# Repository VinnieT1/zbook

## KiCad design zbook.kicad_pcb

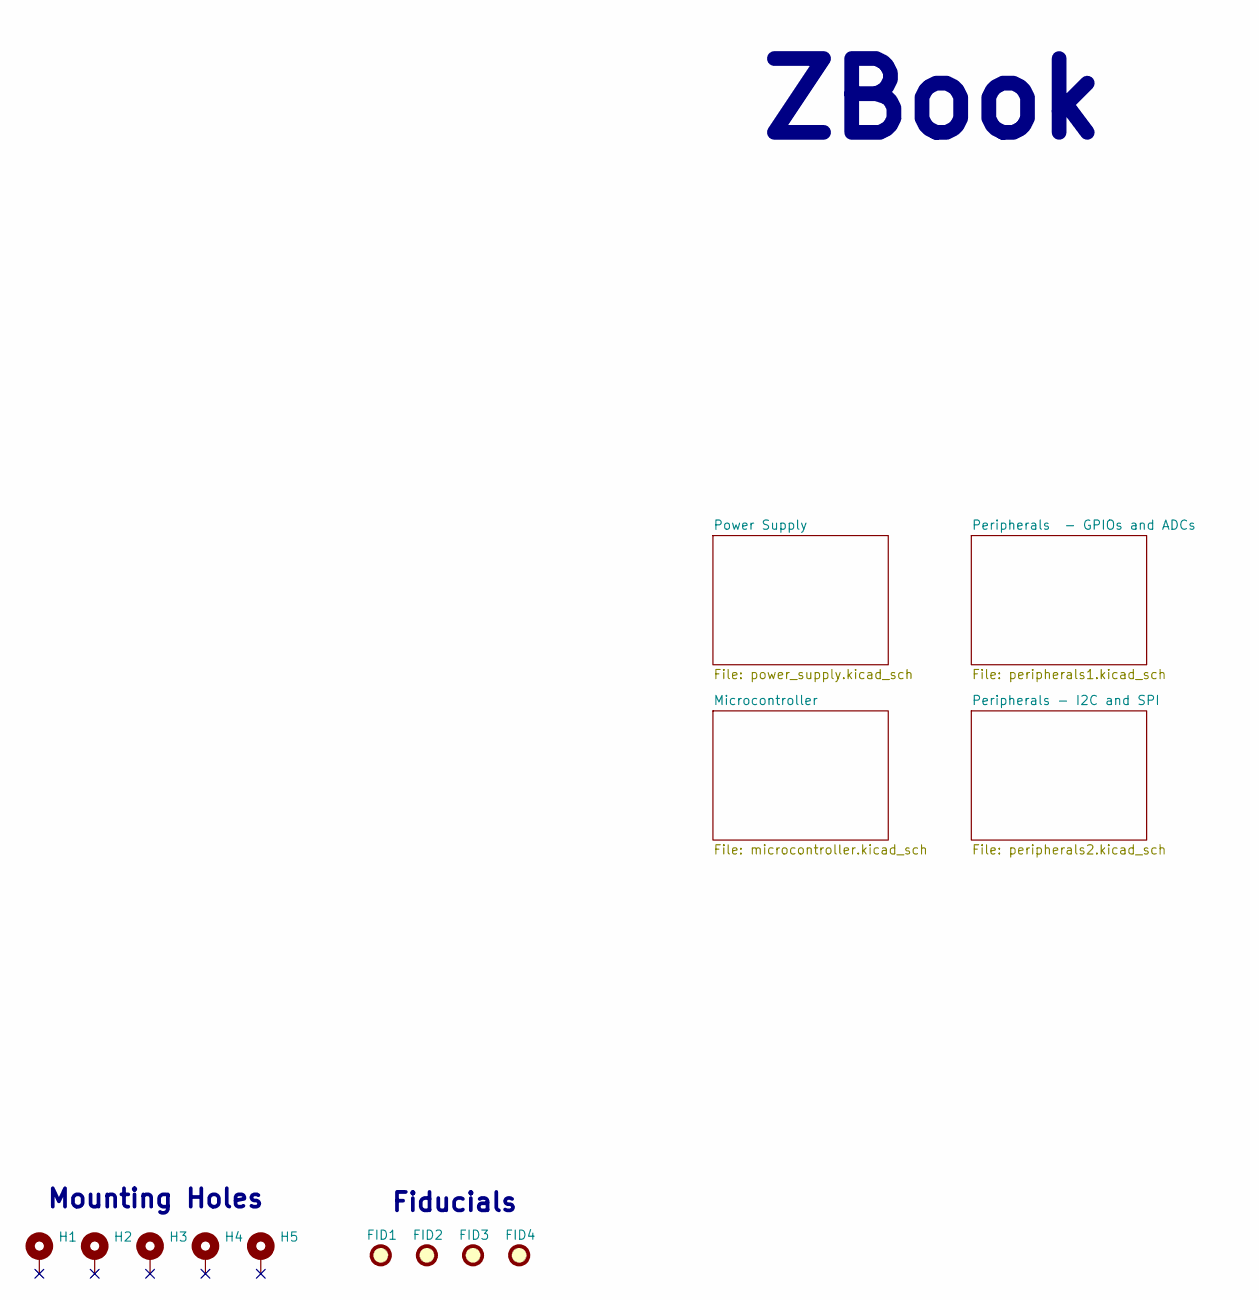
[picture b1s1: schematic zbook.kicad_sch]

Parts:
FID1, FID2, FID3, FID4: Fiducial; Fiducial_1mm_Mask3mm
H1, H2, H3, H4, H5: MountingHole_Pad; MountingHole_3.2mm_M3

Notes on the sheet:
ZBook
Fiducials
Mounting Holes

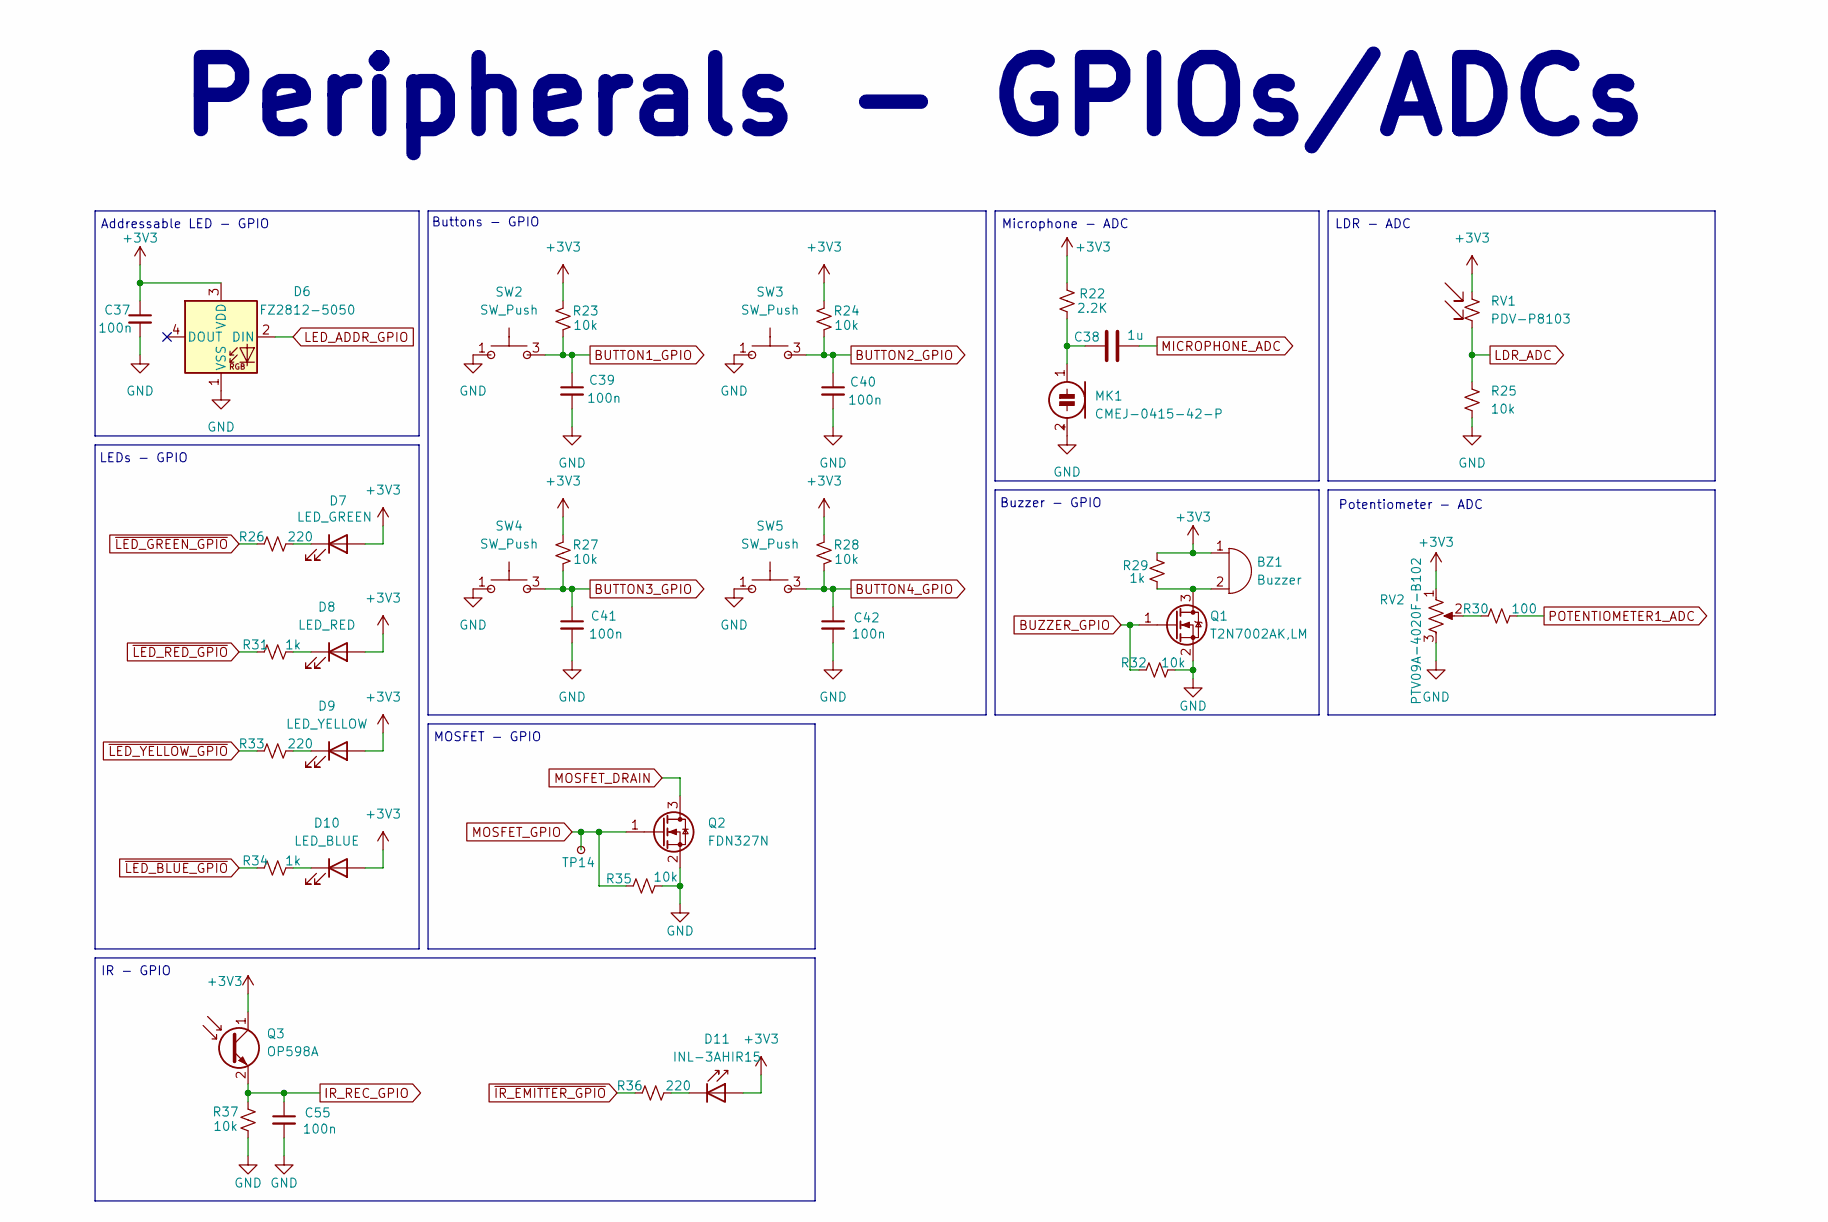
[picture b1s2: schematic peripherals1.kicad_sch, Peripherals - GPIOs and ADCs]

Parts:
BZ1: Buzzer; PS1440P02BT; MPN PS1440P02BT
C37, C39, C40, C41, C42, C55: 100n; C_0402_1005Metric; MPN CL05B104KA5NNNC
C38: 1u; C_0402_1005Metric; MPN CL05A105KO5NNNC
D6: FZ2812-5050; LED_FZ2812-5050; MPN FZ2812-5050
D7: LED_GREEN; LED_0603_1608Metric; MPN LG Q976.01-MGNI-35-1
D8: LED_RED; LED_0603_1608Metric; MPN QBLP601-R3-2943
D9: LED_YELLOW; LED_0603_1608Metric; MPN LY Q976.01-Q1R2-36-1
D10: LED_BLUE; LED_0603_1608Metric; MPN LB Q99G.01-P1R1-35-1-5-R18
D11: INL-3AHIR15; LED_D3.0mm_IRBlack; MPN INL-3AHIR15
MK1: CMEJ-0415-42-P; CMEJ-0415_CUD; MPN CMEJ-0415-42-P
Q1: T2N7002AK,LM; SOT-23; MPN T2N7002AK,LM
Q2: FDN327N; SOT-23; MPN FDN327N
Q3: OP598A; TO-18-2; MPN OP598A
R22: 2.2K; R_0402_1005Metric; MPN ERA-2AEB222X
R23, R24, R25, R27, R28, R32, R35, R37: 10k; R_0402_1005Metric; MPN RC0402JR-0710KL
R26, R33, R36: 220; R_0402_1005Metric; MPN RC0402JR-13220RL
R29, R31, R34: 1k; R_0402_1005Metric; MPN RC0402JR-071KL
R30: 100; R_0402_1005Metric; MPN ERJ-2RKF1000X
RV1: PDV-P8103; R_LDR_5.1x4.3mm_P3.4mm_Vertical; MPN PDV-P8103
RV2: PTV09A-4020F-B102; MPN PTV09A-4020F-B102
SW2, SW3, SW4, SW5: SW_Push; SW_1825910-6-4; MPN 1825910-6
TP14: TestPoint_Small; TestPoint_Pad_D1.0mm

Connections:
+3V3: BZ1.1 (+), C37.1, D6.3 (VDD), D7.2 (A), D8.2 (A), D9.2 (A), D10.2 (A), D11.2 (A), Q3.1 (C), R22.1, R23.2, R24.2, R27.2, R28.2, R29.2, RV1.1, RV2.1; also elsewhere on the board
BUTTON1_GPIO: C39.1, R23.1, SW2.3; also elsewhere on the board
BUTTON2_GPIO: C40.1, R24.1, SW3.3; also elsewhere on the board
BUTTON3_GPIO: C41.1, R27.1, SW4.3; also elsewhere on the board
BUTTON4_GPIO: C42.1, R28.1, SW5.3; also elsewhere on the board
BUZZER_GPIO: Q1.1 (G), R32.1; also elsewhere on the board
GND: C37.2, C39.2, C40.2, C41.2, C42.2, C55.2, D6.1 (VSS), MK1.2 (+), Q1.2 (S), Q2.2 (S), R25.2, R32.2, R35.2, R37.1, RV2.3, SW2.1, SW3.1, SW4.1, SW5.1; also elsewhere on the board
IR_REC_GPIO: C55.1, Q3.2 (E), R37.2; also elsewhere on the board
LDR_ADC: R25.1, RV1.2; also elsewhere on the board
LED_ADDR_GPIO: D6.2 (DIN); also elsewhere on the board
MICROPHONE_ADC: C38.2; also elsewhere on the board
MOSFET_DRAIN: Q2.3 (D); also elsewhere on the board
MOSFET_GPIO: Q2.1 (G), R35.1, TP14.1; also elsewhere on the board
unnamed: BZ1.2 (-), Q1.3 (D), R29.1
unnamed: D7.1 (K), R26.2
unnamed: D8.1 (K), R31.2
unnamed: D9.1 (K), R33.2
unnamed: D10.1 (K), R34.2
unnamed: D11.1 (K), R36.2
unnamed: C38.1, MK1.1 (-), R22.2
unnamed: R30.1, RV2.2
POTENTIOMETER1_ADC: R30.2; also elsewhere on the board
~IR_EMITTER_GPIO: R36.1; also elsewhere on the board
~LED_BLUE_GPIO: R34.1; also elsewhere on the board
~LED_GREEN_GPIO: R26.1; also elsewhere on the board
~LED_RED_GPIO: R31.1; also elsewhere on the board
~LED_YELLOW_GPIO: R33.1; also elsewhere on the board

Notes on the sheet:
Microphone - ADC
Potentiometer - ADC
LDR - ADC
Buttons - GPIO
Peripherals - GPIOs/ADCs
MOSFET - GPIO
Addressable LED - GPIO
IR - GPIO
LEDs - GPIO
Buzzer - GPIO

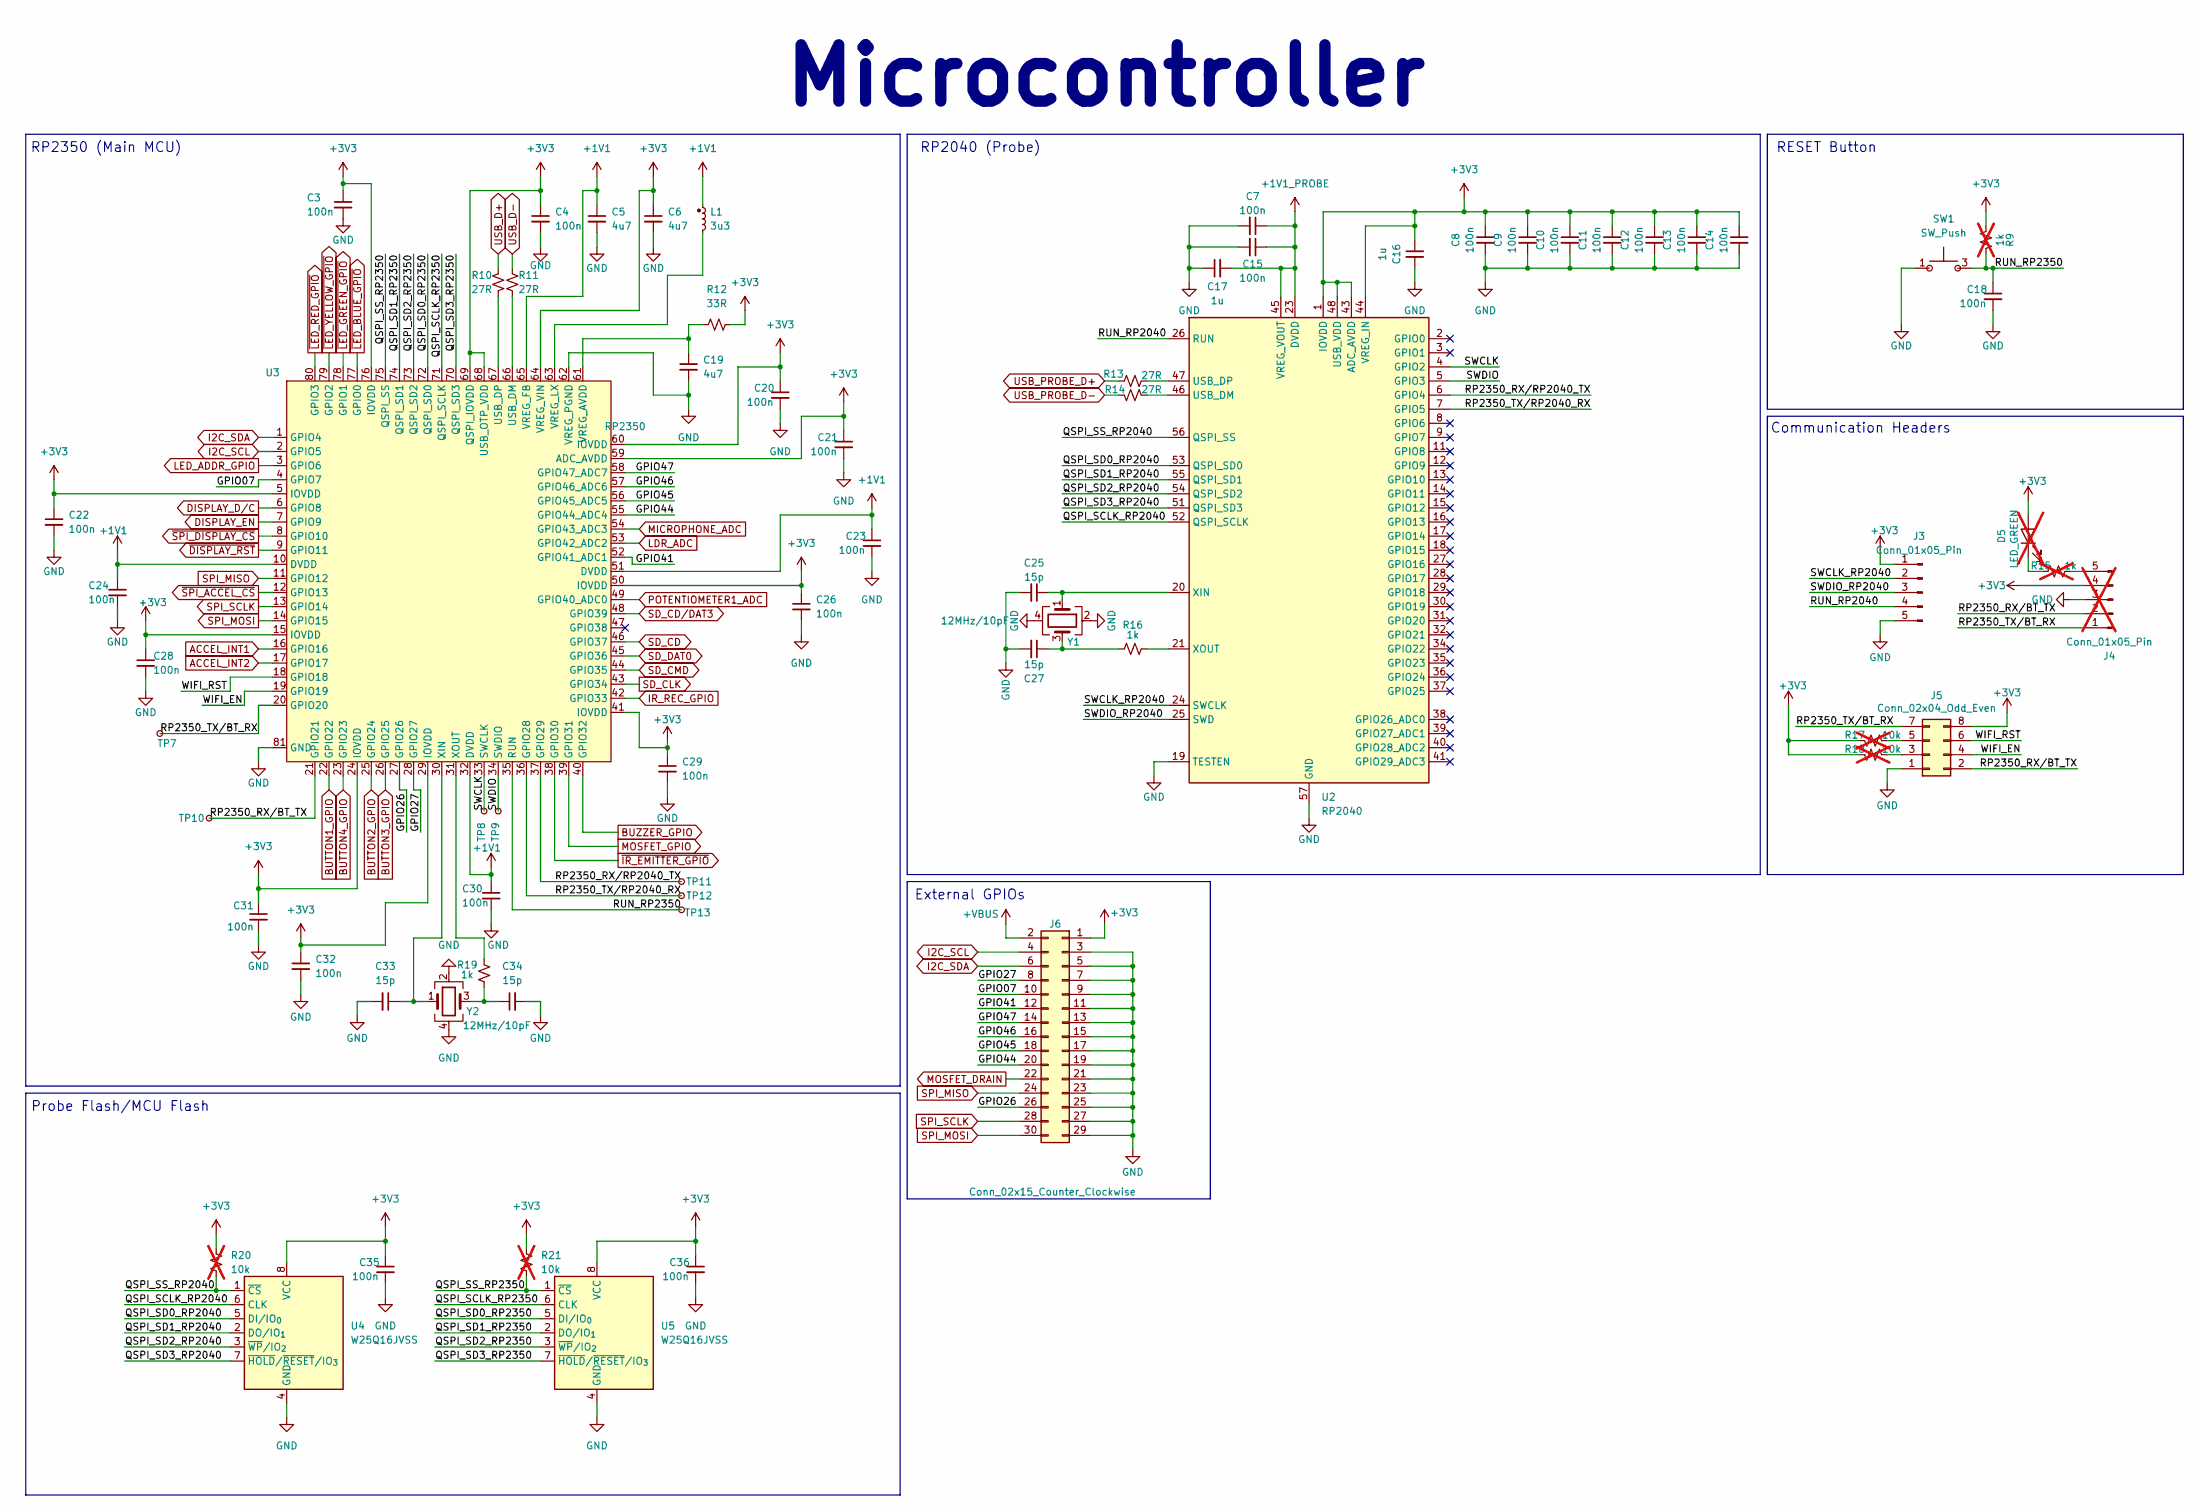
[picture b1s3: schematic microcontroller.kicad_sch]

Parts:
C3, C4, C7, C8, C9, C10, C11, C12, C13, C14, C15, C18, C20, C21, C22, C23, C24, C26, C28, C29, C30, C31, C32, C35, C36: 100n; C_0402_1005Metric; MPN CL05B104KA5NNNC
C5, C6, C19: 4u7; C_0402_1005Metric; MPN CL05A475MP5NRNC
C16, C17: 1u; C_0402_1005Metric; MPN CL05A105KO5NNNC
C25, C27, C33, C34: 15p; C_0402_1005Metric; MPN GCM1555C1H150JA16D
D5: LED_GREEN; LED_0603_1608Metric; MPN LG Q976.01-MGNI-35-1; not fitted
J3: Conn_01x05_Pin; PogoPins
J4: Conn_01x05_Pin; PinHeader_1x05_P2.54mm_Vertical; MPN PH1-05-UA; not fitted
J5: Conn_02x04_Odd_Even; PinSocket_2x04_P2.54mm_Vertical; MPN 61300821821
J6: Conn_02x15_Counter_Clockwise; PinSocket_2x15_P2.54mm_Vertical; MPN PPPC152LFBN-RC
L1: 3u3; L_0805_2012Metric_Pad1.15x1.40mm_HandSolder; MPN AOTA-B201610S3R3-101-T
R9, R15: 1k; R_0402_1005Metric; MPN RC0402JR-071KL; not fitted
R10, R11, R13, R14: 27R; R_0402_1005Metric; MPN RC0402JR-0727RL
R12: 33R; R_0402_1005Metric; MPN RC0402JR-0733RL
R16, R19: 1k; R_0402_1005Metric; MPN RC0402JR-071KL
R17, R18, R20, R21: 10k; R_0402_1005Metric; MPN RC0402JR-0710KL; not fitted
SW1: SW_Push; SW_1825910-6-4; MPN 1825910-6
TP7, TP8, TP9, TP10, TP11, TP12, TP13: TestPoint_Small; TestPoint_Pad_D1.0mm
U2: RP2040; QFN-56-1EP_7x7mm_P0.4mm_EP3.2x3.2mm_ThermalVias; MPN SC0914(13)
U3: RP2350; QFN-80_EP_14x14_Pitch0.4mm; MPN SC1510
U4, U5: W25Q16JVSS; SOIC-8_5.3x5.3mm_P1.27mm; MPN W25Q16JVSSIQ
Y1, Y2: 12MHz/10pF; XTAL_ABM8-272-T3; MPN ABM8-272-T3

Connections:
+1V1: C5.1, C23.1, C24.1, C30.1, L1.1, U3.10 (DVDD), U3.32 (DVDD), U3.51 (DVDD), U3.65 (VREG_FB)
+1V1_PROBE: C7.1, C15.1, C17.2, U2.23 (DVDD), U2.45 (VREG_VOUT), U2.50 (DVDD)
+3V3: C3.1, C4.1, C6.1, C8.1, C9.1, C10.1, C11.1, C12.1, C13.1, C14.1, C16.1, C20.1, C21.1, C22.1, C26.1, C28.1, C29.1, C31.1, C32.1, C35.1, C36.1, D5.2 (A), J3.1, J4.4, J5.8, J6.1, R9.2, R12.2, R17.2, R18.2, R20.1, R21.1, U2.1 (IOVDD), U2.10 (IOVDD), U2.22 (IOVDD), U2.33 (IOVDD), U2.42 (IOVDD), U2.43 (ADC_AVDD), U2.44 (VREG_IN), U2.48 (USB_VDD), U2.49 (IOVDD), U3.5 (IOVDD), U3.15 (IOVDD), U3.24 (IOVDD), U3.29 (IOVDD), U3.41 (IOVDD), U3.50 (IOVDD), U3.59 (ADC_AVDD), U3.60 (IOVDD), U3.64 (VREG_VIN), U3.68 (USB_OTP_VDD), U3.69 (QSPI_IOVDD), U3.76 (IOVDD), U4.8 (VCC), U5.8 (VCC); also elsewhere on the board
+VBUS: J6.2; also elsewhere on the board
/Microcontroller/GPIO07: J6.10, U3.4 (GPIO7)
/Microcontroller/GPIO26: J6.26, U3.27 (GPIO26)
/Microcontroller/GPIO27: J6.8, U3.28 (GPIO27)
/Microcontroller/GPIO41: J6.12, U3.52 (GPIO41_ADC1)
/Microcontroller/GPIO44: J6.20, U3.55 (GPIO44_ADC4)
/Microcontroller/GPIO45: J6.18, U3.56 (GPIO45_ADC5)
/Microcontroller/GPIO46: J6.16, U3.57 (GPIO46_ADC6)
/Microcontroller/GPIO47: J6.14, U3.58 (GPIO47_ADC7)
/Microcontroller/QSPI_SCLK_RP2040: U2.52 (QSPI_SCLK), U4.6 (CLK)
/Microcontroller/QSPI_SCLK_RP2350: U3.71 (QSPI_SCLK), U5.6 (CLK)
/Microcontroller/QSPI_SD0_RP2040: U2.53 (QSPI_SD0), U4.5 (DI/IO_{0})
/Microcontroller/QSPI_SD0_RP2350: U3.72 (QSPI_SD0), U5.5 (DI/IO_{0})
/Microcontroller/QSPI_SD1_RP2040: U2.55 (QSPI_SD1), U4.2 (DO/IO_{1})
/Microcontroller/QSPI_SD1_RP2350: U3.74 (QSPI_SD1), U5.2 (DO/IO_{1})
/Microcontroller/QSPI_SD2_RP2040: U2.54 (QSPI_SD2), U4.3 (~WP/IO_{2})
/Microcontroller/QSPI_SD2_RP2350: U3.73 (QSPI_SD2), U5.3 (~WP/IO_{2})
/Microcontroller/QSPI_SD3_RP2040: U2.51 (QSPI_SD3), U4.7 (~HOLD/~RESET/IO_{3})
/Microcontroller/QSPI_SD3_RP2350: U3.70 (QSPI_SD3), U5.7 (~HOLD/~RESET/IO_{3})
/Microcontroller/QSPI_SS_RP2040: R20.2, U2.56 (QSPI_SS), U4.1 (~CS)
/Microcontroller/QSPI_SS_RP2350: R21.2, U3.75 (QSPI_SS), U5.1 (~CS)
/Microcontroller/RP2350_RX/BT_TX: J4.2, J5.2, TP10.1, U3.21 (GPIO21)
/Microcontroller/RP2350_RX/RP2040_TX: TP11.1, U2.6 (GPIO4), U3.37 (GPIO29)
/Microcontroller/RP2350_TX/BT_RX: J4.1, J5.7, TP7.1, U3.20 (GPIO20)
/Microcontroller/RP2350_TX/RP2040_RX: TP12.1, U2.7 (GPIO5), U3.36 (GPIO28)
/Microcontroller/RUN_RP2040: J3.4, U2.26 (RUN)
/Microcontroller/RUN_RP2350: C18.1, R9.1, SW1.3, TP13.1, U3.35 (RUN)
/Microcontroller/SWCLK: TP8.1, U2.4 (GPIO2), U3.33 (SWCLK)
/Microcontroller/SWCLK_RP2040: J3.2, U2.24 (SWCLK)
/Microcontroller/SWDIO: TP9.1, U2.5 (GPIO3), U3.34 (SWDIO)
/Microcontroller/SWDIO_RP2040: J3.3, U2.25 (SWD)
/Microcontroller/WIFI_EN: J5.4, U3.19 (GPIO19)
/Microcontroller/WIFI_RST: J5.6, U3.18 (GPIO18)
ACCEL_INT1: U3.16 (GPIO16); also elsewhere on the board
ACCEL_INT2: U3.17 (GPIO17); also elsewhere on the board
BUTTON1_GPIO: U3.22 (GPIO22); also elsewhere on the board
BUTTON2_GPIO: U3.25 (GPIO24); also elsewhere on the board
BUTTON3_GPIO: U3.26 (GPIO25); also elsewhere on the board
BUTTON4_GPIO: U3.23 (GPIO23); also elsewhere on the board
BUZZER_GPIO: U3.40 (GPIO32); also elsewhere on the board
DISPLAY_D/C: U3.6 (GPIO8); also elsewhere on the board
DISPLAY_EN: U3.7 (GPIO9); also elsewhere on the board
GND: C3.2, C4.2, C5.2, C6.2, C7.2, C8.2, C9.2, C10.2, C11.2, C12.2, C13.2, C14.2, C15.2, C16.2, C17.1, C18.2, C19.2, C20.2, C21.2, C22.2, C23.2, C24.2, C25.2, C26.2, C27.2, C28.2, C29.2, C30.2, C31.2, C32.2, C33.2, C34.2, C35.2, C36.2, J3.5, J4.3, J5.1, J6.3, J6.5, J6.7, J6.9, J6.11, J6.13, J6.15, J6.17, J6.19, J6.21, J6.23, J6.25, J6.27, J6.29, SW1.1, U2.19 (TESTEN), U2.57 (GND), U3.62 (VREG_PGND), U3.81 (GND), U4.4 (GND), U5.4 (GND), Y1.2, Y1.4, Y2.2, Y2.4; also elsewhere on the board
I2C_SCL: J6.4, U3.2 (GPIO5); also elsewhere on the board
I2C_SDA: J6.6, U3.1 (GPIO4); also elsewhere on the board
IR_REC_GPIO: U3.42 (GPIO33); also elsewhere on the board
LDR_ADC: U3.53 (GPIO42_ADC2); also elsewhere on the board
LED_ADDR_GPIO: U3.3 (GPIO6); also elsewhere on the board
MICROPHONE_ADC: U3.54 (GPIO43_ADC3); also elsewhere on the board
MOSFET_DRAIN: J6.22; also elsewhere on the board
MOSFET_GPIO: U3.39 (GPIO31); also elsewhere on the board
unnamed: C27.1, R16.1, Y1.3
unnamed: C34.1, R19.1, Y2.3
unnamed: D5.1 (K), R15.1
unnamed: J4.5, R15.2
unnamed: J5.3, R18.1
unnamed: J5.5, R17.1
unnamed: R14.2, U2.46 (USB_DM)
unnamed: R13.2, U2.47 (USB_DP)
unnamed: C25.1, U2.20 (XIN), Y1.1
unnamed: R16.2, U2.21 (XOUT)
unnamed: R11.2, U3.66 (USB_DM)
unnamed: R10.2, U3.67 (USB_DP)
unnamed: C19.1, R12.1, U3.61 (VREG_AVDD)
unnamed: L1.2, U3.63 (VREG_LX)
unnamed: C33.1, U3.30 (XIN), Y2.1
unnamed: R19.2, U3.31 (XOUT)
POTENTIOMETER1_ADC: U3.49 (GPIO40_ADC0); also elsewhere on the board
SD_CD: U3.46 (GPIO37); also elsewhere on the board
SD_CD/DAT3: U3.48 (GPIO39); also elsewhere on the board
SD_CLK: U3.43 (GPIO34); also elsewhere on the board
SD_CMD: U3.44 (GPIO35); also elsewhere on the board
SD_DAT0: U3.45 (GPIO36); also elsewhere on the board
SPI_MISO: J6.24, U3.11 (GPIO12); also elsewhere on the board
SPI_MOSI: J6.30, U3.14 (GPIO15); also elsewhere on the board
SPI_SCLK: J6.28, U3.13 (GPIO14); also elsewhere on the board
USB_D+: R10.1; also elsewhere on the board
USB_D-: R11.1; also elsewhere on the board
USB_PROBE_D+: R13.1; also elsewhere on the board
USB_PROBE_D-: R14.1; also elsewhere on the board
~DISPLAY_RST: U3.9 (GPIO11); also elsewhere on the board
~IR_EMITTER_GPIO: U3.38 (GPIO30); also elsewhere on the board
~LED_BLUE_GPIO: U3.77 (GPIO0); also elsewhere on the board
~LED_GREEN_GPIO: U3.78 (GPIO1); also elsewhere on the board
~LED_RED_GPIO: U3.80 (GPIO3); also elsewhere on the board
~LED_YELLOW_GPIO: U3.79 (GPIO2); also elsewhere on the board
~SPI_ACCEL_CS: U3.12 (GPIO13); also elsewhere on the board
~SPI_DISPLAY_CS: U3.8 (GPIO10); also elsewhere on the board

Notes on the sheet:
Microcontroller
RP2350 (Main MCU)
Communication Headers
RESET Button
RP2040 (Probe)
External GPIOs
Probe Flash/MCU Flash

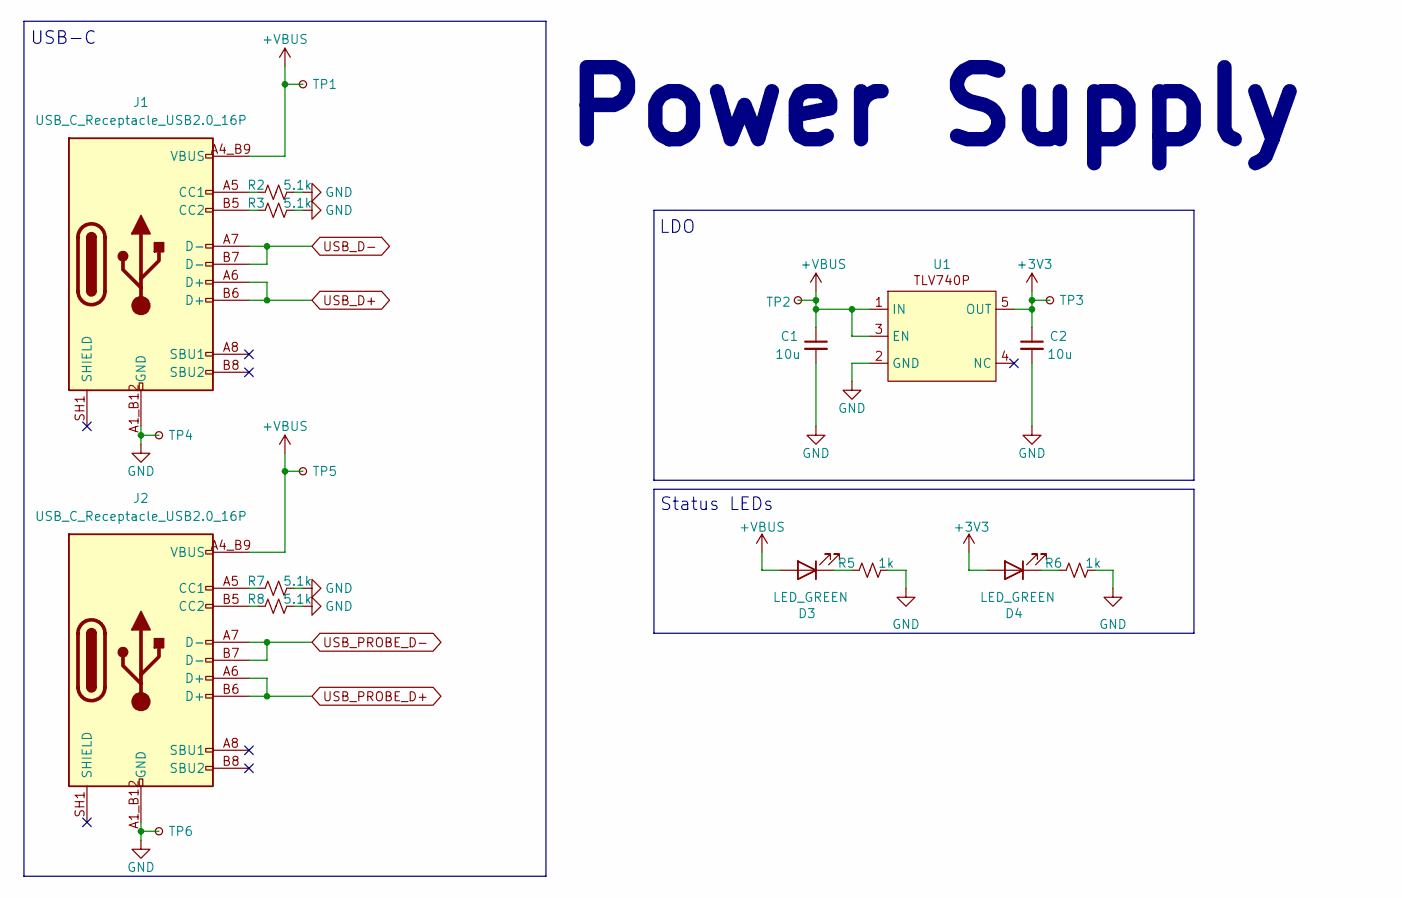
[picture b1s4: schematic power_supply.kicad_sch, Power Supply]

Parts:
C1, C2: 10u; C_0805_2012Metric; MPN CL21A106KOQNNNG
D3, D4: LED_GREEN; LED_0603_1608Metric; MPN LG Q976.01-MGNI-35-1
J1, J2: USB_C_Receptacle_USB2.0_16P; SAMESKY_UJ20-C-H-G-SMT-1-P16-TR; MPN UJ20-C-H-G-SMT-1-P16-TR
R2, R3, R7, R8: 5.1k; R_0402_1005Metric; MPN AC0402FR-075K1L
R5, R6: 1k; R_0402_1005Metric; MPN RC0402JR-071KL
TP1, TP2, TP3, TP4, TP5, TP6: TestPoint_Small; TestPoint_Pad_D1.0mm
U1: TLV78533PDBVR; DBV0005A-IPC_B; MPN TLV78533PDBVR

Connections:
+3V3: C2.1, D4.2 (A), TP3.1, U1.5 (OUT); also elsewhere on the board
+VBUS: C1.1, D3.2 (A), J1.A4_B9 (VBUS), J1.B4_A9 (VBUS), J2.A4_B9 (VBUS), J2.B4_A9 (VBUS), TP1.1, TP2.1, TP5.1, U1.1 (IN), U1.3 (EN); also elsewhere on the board
GND: C1.2, C2.2, J1.A1_B12 (GND), J1.B1_A12 (GND), J2.A1_B12 (GND), J2.B1_A12 (GND), R2.2, R3.2, R5.1, R6.1, R7.2, R8.2, TP4.1, TP6.1, U1.2 (GND); also elsewhere on the board
unnamed: D3.1 (K), R5.2
unnamed: D4.1 (K), R6.2
unnamed: J1.A5 (CC1), R2.1
unnamed: J1.B5 (CC2), R3.1
unnamed: J2.A5 (CC1), R7.1
unnamed: J2.B5 (CC2), R8.1
USB_D+: J1.A6 (D+), J1.B6 (D+); also elsewhere on the board
USB_D-: J1.A7 (D-), J1.B7 (D-); also elsewhere on the board
USB_PROBE_D+: J2.A6 (D+), J2.B6 (D+); also elsewhere on the board
USB_PROBE_D-: J2.A7 (D-), J2.B7 (D-); also elsewhere on the board

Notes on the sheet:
Status LEDs
USB-C
Power Supply
LDO

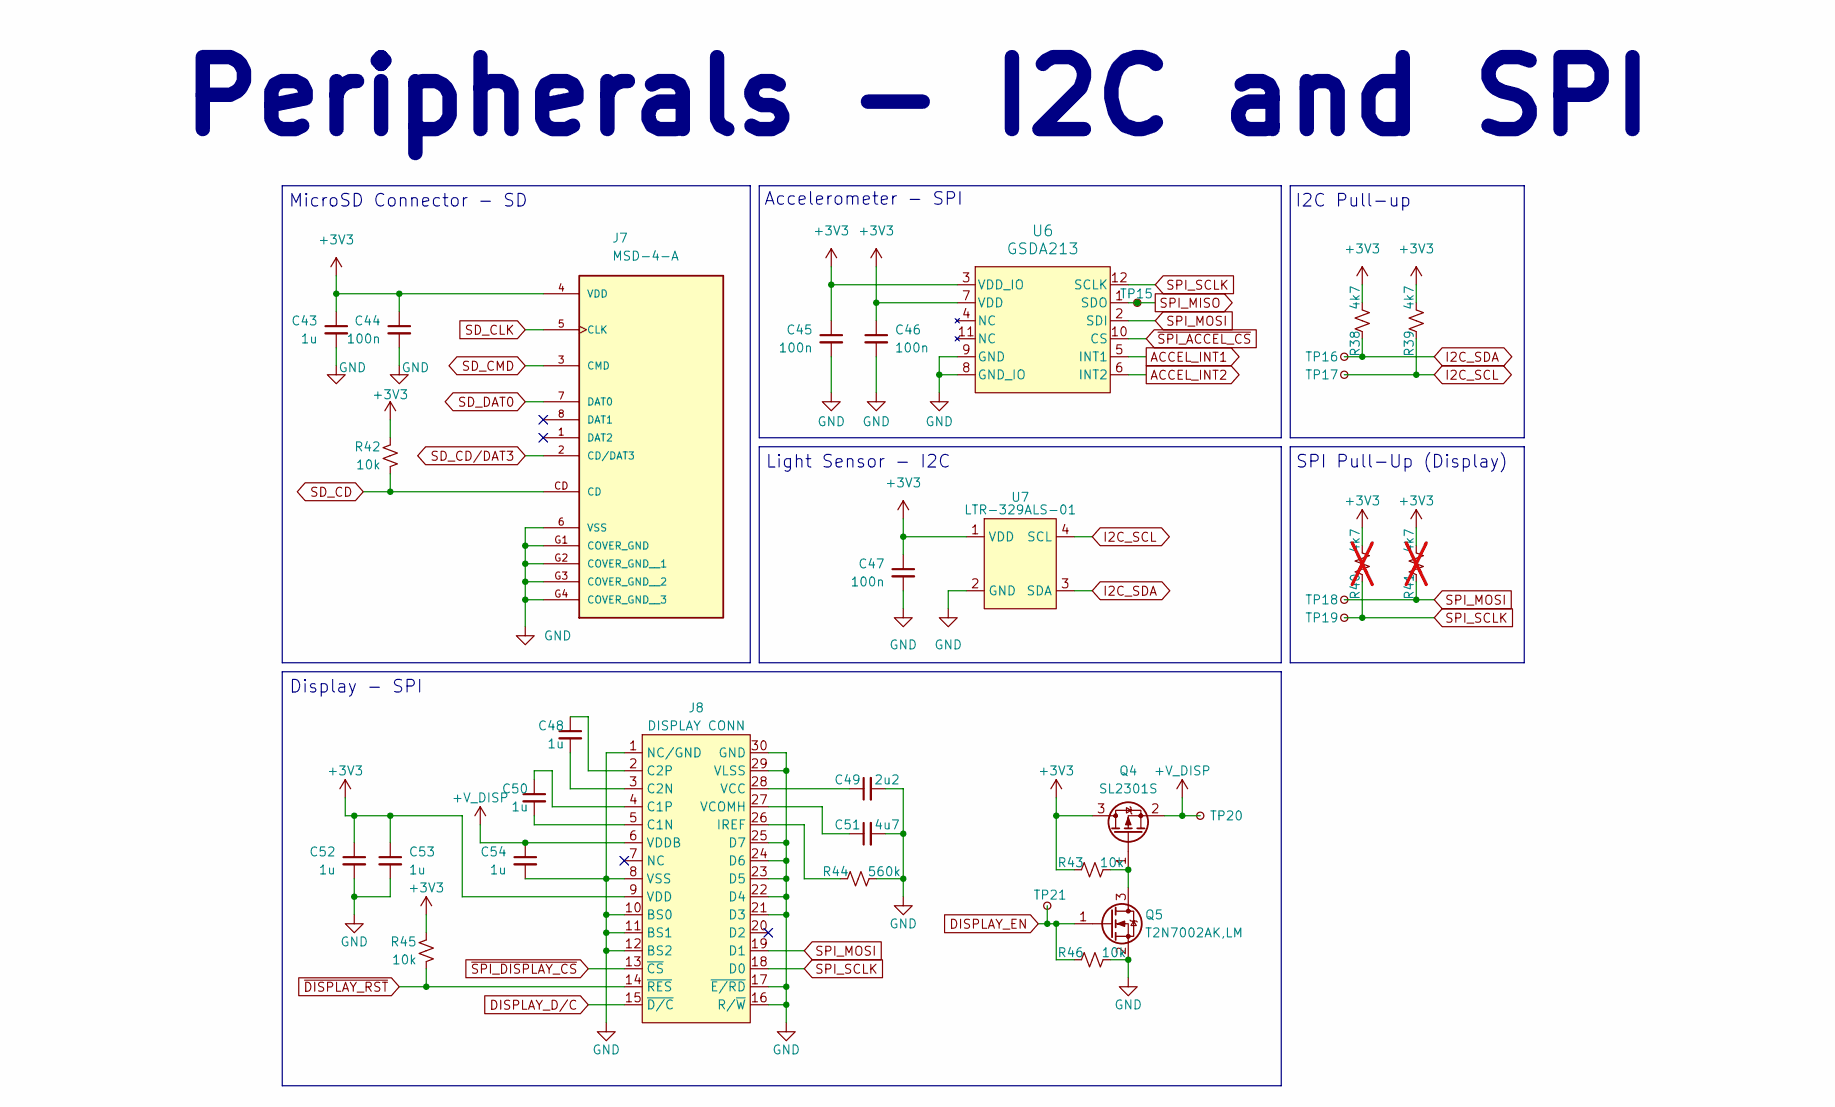
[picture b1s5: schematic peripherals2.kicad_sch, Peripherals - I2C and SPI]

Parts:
C43, C48, C50, C52, C53, C54: 1u; C_0402_1005Metric; MPN CL05A105KO5NNNC
C44, C45, C46, C47: 100n; C_0402_1005Metric; MPN CL05B104KA5NNNC
C49: 2u2; C_0402_1005Metric; MPN CL05A225KO5NQNC
C51: 4u7; C_0402_1005Metric; MPN CL05A475MP5NRNC
J7: MSD-4-A; CUI_MSD-4-A; PARTREV 1.0
J8: DISPLAY CONN; FPC_30
Q4: SL2301S; SOT-23; MPN SL2301S
Q5: T2N7002AK,LM; SOT-23; MPN T2N7002AK,LM
R38, R39: 4k7; R_0402_1005Metric; MPN RC0402JR-074K7L
R40, R41: 4k7; R_0402_1005Metric; MPN RC0402JR-074K7L; not fitted
R42, R43, R45, R46: 10k; R_0402_1005Metric; MPN RC0402JR-0710KL
R44: 560k; R_0402_1005Metric; MPN RC0402JR-07560KL
TP15, TP16, TP17, TP18, TP19, TP20, TP21: TestPoint_Small; TestPoint_Pad_D1.0mm
U6: GSDA213; LGA12_GAS-M; MPN GSDA213
U7: LTR-329ALS-01; LTR-329ALS-01_LTO-M; MPN LTR-329ALS-01

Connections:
+3V3: C43.1, C44.1, C45.1, C46.1, C47.1, C52.1, C53.1, J7.4 (VDD), J8.9 (VDD), Q4.3 (D), R38.2, R39.2, R40.2, R41.2, R42.1, R43.1, R45.1, U6.3 (VDD_IO), U6.7 (VDD), U7.1 (VDD); also elsewhere on the board
+V_DISP: C54.1, J8.6 (VDDB), Q4.2 (S), TP20.1
ACCEL_INT1: U6.5 (INT1); also elsewhere on the board
ACCEL_INT2: U6.6 (INT2); also elsewhere on the board
DISPLAY_D/C: J8.15 (~D/C); also elsewhere on the board
DISPLAY_EN: Q5.1 (G), R46.1, TP21.1; also elsewhere on the board
GND: C43.2, C44.2, C45.2, C46.2, C47.2, C49.2, C51.2, C52.2, C53.2, C54.2, J7.6 (VSS), J7.G1 (COVER_GND), J7.G2 (COVER_GND__1), J7.G3 (COVER_GND__2), J7.G4 (COVER_GND__3), J8.1 (NC/GND), J8.8 (VSS), J8.10 (BS0), J8.11 (BS1), J8.12 (BS2), J8.16 (R/~W), J8.17 (~E/RD), J8.21 (D3), J8.22 (D4), J8.23 (D5), J8.24 (D6), J8.25 (D7), J8.29 (VLSS), J8.30 (GND), Q5.2 (S), R44.2, R46.2, U6.8 (GND_IO), U6.9 (GND), U7.2 (GND); also elsewhere on the board
I2C_SCL: R39.1, TP17.1, U7.4 (SCL); also elsewhere on the board
I2C_SDA: R38.1, TP16.1, U7.3 (SDA); also elsewhere on the board
unnamed: C50.2, J8.5 (C1N)
unnamed: C50.1, J8.4 (C1P)
unnamed: C48.2, J8.3 (C2N)
unnamed: C48.1, J8.2 (C2P)
unnamed: J8.26 (IREF), R44.1
unnamed: C49.1, J8.28 (VCC)
unnamed: C51.1, J8.27 (VCOMH)
unnamed: Q4.1 (G), Q5.3 (D), R43.2
SD_CD: J7.CD, R42.2; also elsewhere on the board
SD_CD/DAT3: J7.2 (CD/DAT3); also elsewhere on the board
SD_CLK: J7.5 (CLK); also elsewhere on the board
SD_CMD: J7.3 (CMD); also elsewhere on the board
SD_DAT0: J7.7 (DAT0); also elsewhere on the board
SPI_MISO: TP15.1, U6.1 (SDO); also elsewhere on the board
SPI_MOSI: J8.19 (D1), R41.1, TP18.1, U6.2 (SDI); also elsewhere on the board
SPI_SCLK: J8.18 (D0), R40.1, TP19.1, U6.12 (SCLK); also elsewhere on the board
~DISPLAY_RST: J8.14 (~RES), R45.2; also elsewhere on the board
~SPI_ACCEL_CS: U6.10 (CS); also elsewhere on the board
~SPI_DISPLAY_CS: J8.13 (~CS); also elsewhere on the board

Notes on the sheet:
Light Sensor - I2C
MicroSD Connector - SD
I2C Pull-up
Accelerometer - SPI
SPI Pull-Up (Display)
Peripherals - I2C and SPI
Display - SPI

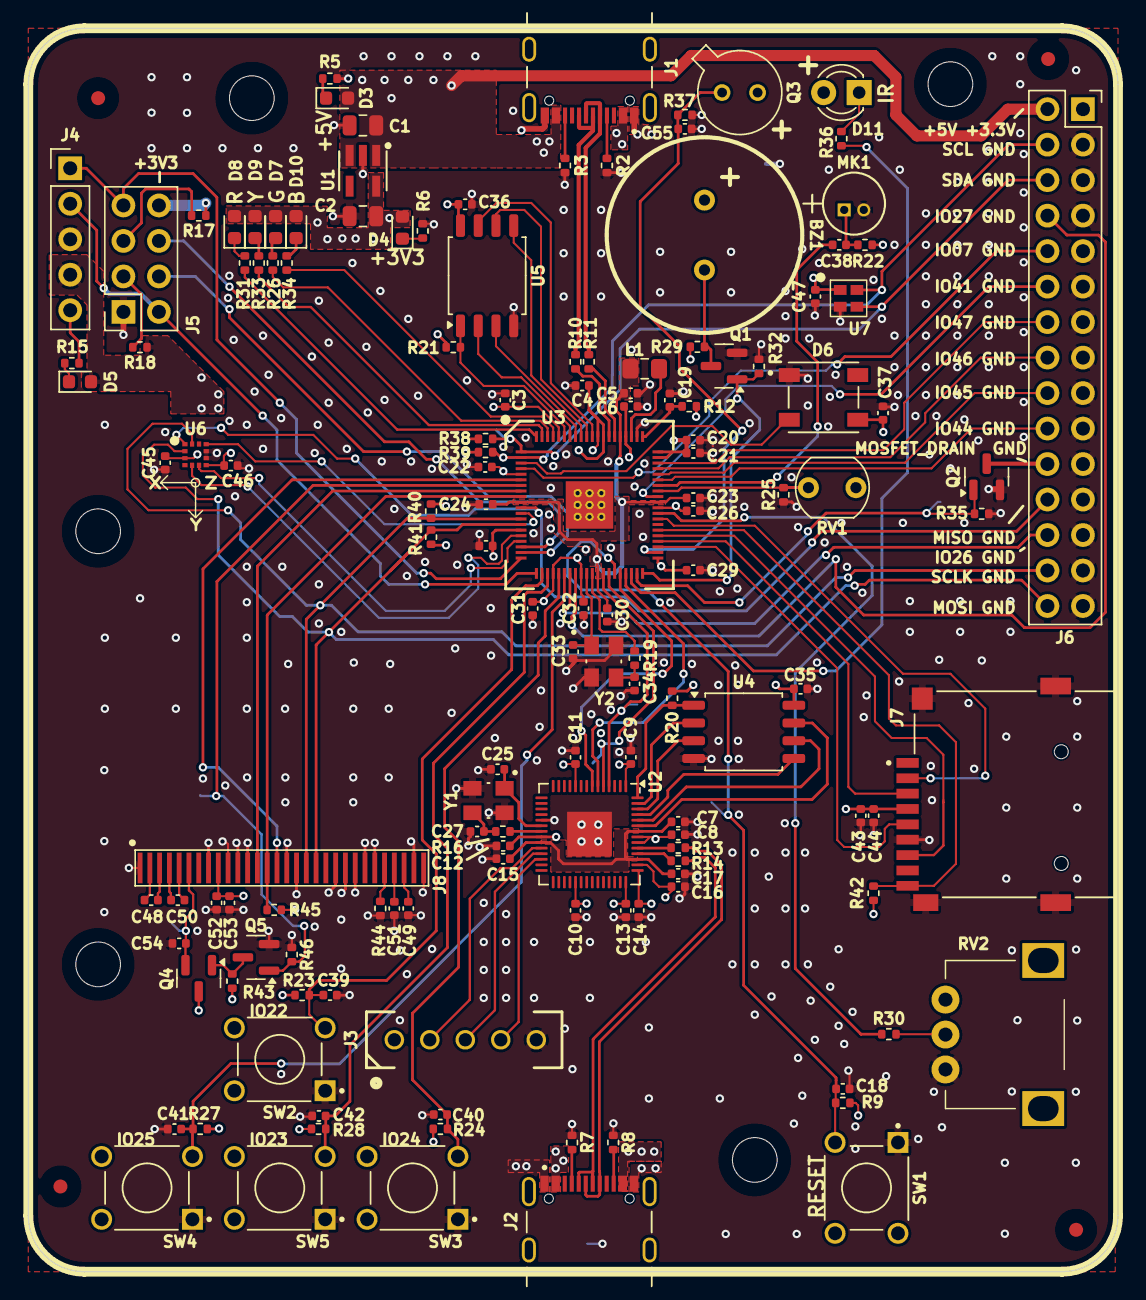
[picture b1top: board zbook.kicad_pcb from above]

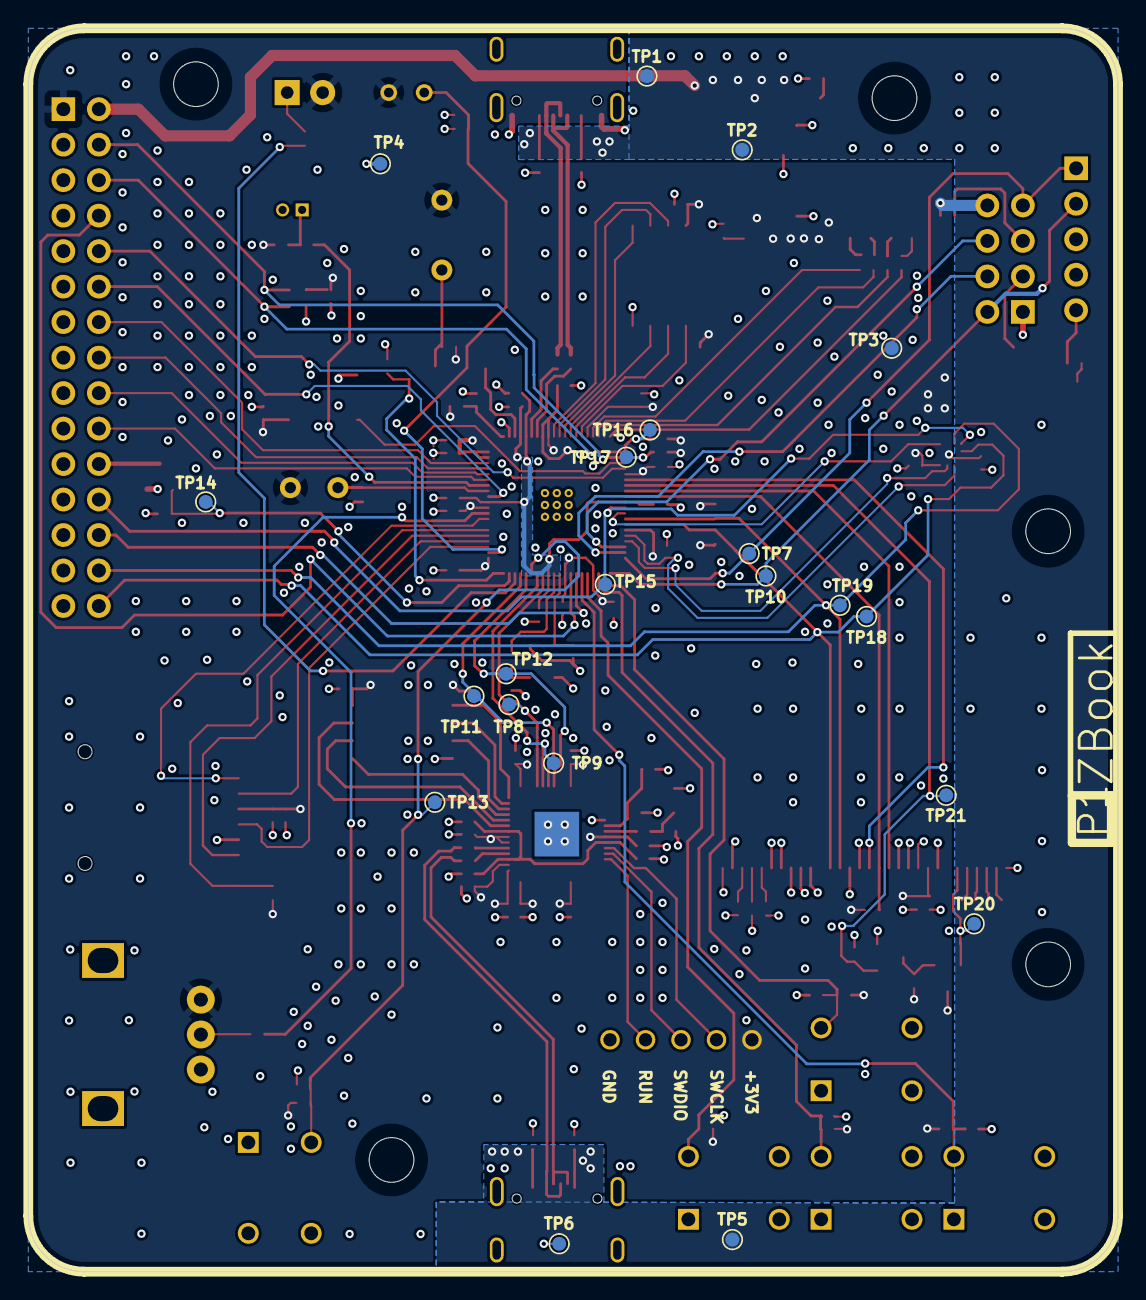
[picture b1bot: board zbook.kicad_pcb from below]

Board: 4 copper layers, 78.0 x 89.0 mm, 170 parts (21 on the bottom side), 114 nets.
